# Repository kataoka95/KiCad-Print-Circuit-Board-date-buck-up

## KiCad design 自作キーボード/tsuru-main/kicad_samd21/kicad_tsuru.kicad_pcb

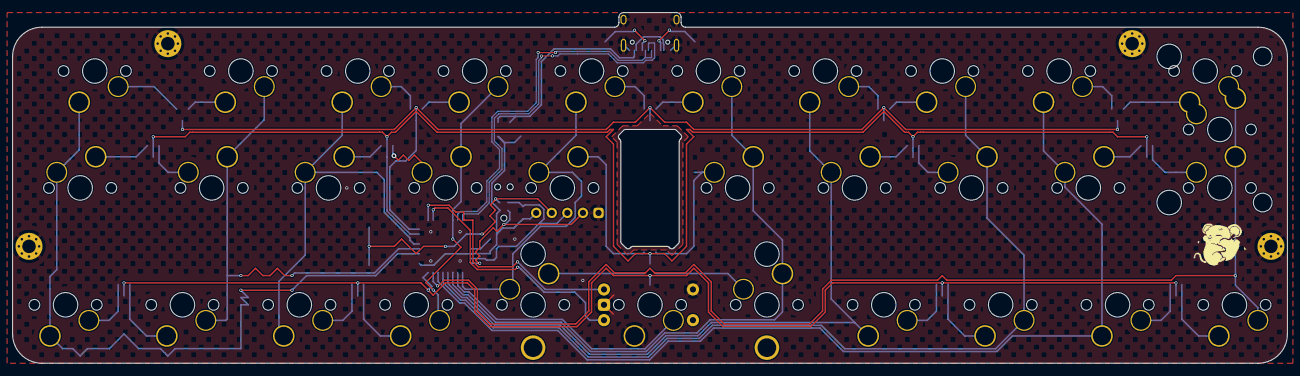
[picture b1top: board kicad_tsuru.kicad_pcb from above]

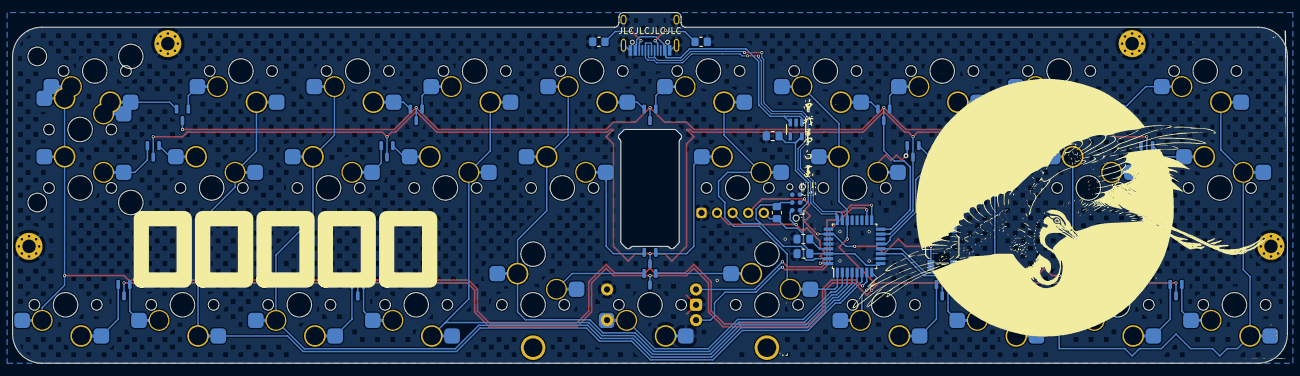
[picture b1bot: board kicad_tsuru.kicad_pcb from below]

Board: 2 copper layers, 207.8 x 57.2 mm, 67 parts (27 on the bottom side), 57 nets.

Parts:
C1, C3: 1nF; C_0805_2012Metric_Pad1.18x1.45mm_HandSolder
C2: 100nF; C_0805_2012Metric_Pad1.18x1.45mm_HandSolder
D1, D2, D3, D4, D5, D6, D7, D8, D9, D10, D11, D12, D13, D14, D15: BAV70_Small; apfel_SOT-23_silkless
H1, H2, H3, H4: MountingHole_Pad; MountingHole_2.2mm_M2_Pad_Via_nosilk
J1: USB_C_Receptacle_USB2.0; USB_C_Receptacle_GT-USB-7010
J2: Conn_ARM_SWD_TagConnect_TC2030-NL; Tag-Connect_TC2030-IDC-NL_2x03_P1.27mm_Vertical
J3: Conn_01x05_Pin; PinHeader_1x05_P2.54mm_Vertical
MX1, MX2, MX3, MX4, MX5, MX6, MX7, MX8, MX9, MX10, MX11, MX12, MX13, MX14, MX15, MX16, MX17, MX18, MX19, MX20, MX21, MX22, MX23, MX24, MX25, MX26, MX27, MX28, MX29, MX30, MX31, MX32: MX_SW_HS; MX-HotswapSAFE_no_silk
R1, R2: 5.1k; R_0805_2012Metric_Pad1.20x1.40mm_HandSolder
R3: 1k; R_0805_2012Metric_Pad1.20x1.40mm_HandSolder
S1: MX_stab; STAB_MX_P_3u
S2: MX_stab; STAB_MX_ISO-ROT
SW1: RotaryEncoder_Switch; ROT_Alps_EC11E-Switch_noMP_nosilk
SW2: SKQGAKE020; SW_SPST_SKQG_WithStem
U1: ATSAMD21E17D-A; TQFP-32_7x7mm_P0.8mm
U2: AP2112K-3.3; SOT-23-5
tsuru: LOGO

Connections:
+3.3V: C1.1, C2.1, J2.1 (VCC), J3.5, R3.1, U1.9 (VDDANA), U1.30 (VDDIN), U2.5 (VOUT)
+5V: J1.A4 (VBUS), J1.A9 (VBUS), J1.B4 (VBUS), J1.B9 (VBUS), U2.1 (VIN), U2.3 (EN)
D+: J1.A6 (D+), J1.B6 (D+), U1.24 (PA25)
D-: J1.A7 (D-), J1.B7 (D-), U1.23 (PA24)
ENC_LEFT: SW1.B, U1.18 (PA17)
ENC_RIGHT: SW1.A, U1.17 (PA16)
Enc_direct_pin: MX31.1, SW1.S1, U1.2 (PA01)
GND: C1.2, C2.2, C3.1, H1.1, H2.1, H3.1, H4.1, J1.A1 (GND), J1.A12 (GND), J1.B1 (GND), J1.B12 (GND), J1.S1 (SHIELD), J2.5 (GND), J3.1, MX31.2, R1.2, R2.2, SW1.C, SW1.S2, SW2.2, U1.10 (GND), U1.28 (GND), U2.2 (GND)
unnamed: D1.1 (A1), MX1.1
unnamed: D1.2 (A2), MX2.2
unnamed: D2.1 (A1), MX3.1
unnamed: D2.2 (A2), MX4.2
unnamed: D3.1 (A1), MX5.1
unnamed: D3.2 (A2), MX6.2
unnamed: D4.1 (A1), MX7.1
unnamed: D4.2 (A2), MX8.2
unnamed: D5.1 (A1), MX9.1
unnamed: D5.2 (A2), MX10.2, MX32.1
unnamed: D6.1 (A1), MX11.2
unnamed: D6.2 (A2), MX12.1
unnamed: D7.1 (A1), MX13.2
unnamed: D7.2 (A2), MX14.1
unnamed: D8.1 (A1), MX15.2
unnamed: D8.2 (A2), MX16.1
unnamed: D9.1 (A1), MX17.2
unnamed: D9.2 (A2), MX18.1
unnamed: D10.1 (A1), MX19.2
unnamed: D10.2 (A2), MX20.1
unnamed: D11.1 (A1), MX21.1
unnamed: D11.2 (A2), MX22.2
unnamed: D12.1 (A1), MX23.1
unnamed: D12.2 (A2), MX24.2
unnamed: D13.1 (A1), MX25.2
unnamed: D13.2 (A2), MX26.1
unnamed: D14.1 (A1), MX27.1
unnamed: D14.2 (A2), MX28.2
unnamed: D15.1 (A1), MX29.1
unnamed: D15.2 (A2), MX30.2
unnamed: J1.A5 (CC1), R1.1
unnamed: J1.B5 (CC2), R2.1
unnamed: C3.2, U1.29 (VDDCORE)
RESET: J2.3 (~RESET), J3.4, SW2.1, U1.26 (~RESET)
SWCLK: J2.4 (SWCLK), J3.3, R3.2, U1.31 (PA30)
SWDIO: J2.2 (SWDIO), J3.2, U1.32 (PA31)
c0: MX1.2, MX11.1, MX21.2, U1.11 (PA08)
c1: MX2.1, MX12.2, MX22.1, U1.12 (PA09)
c2: MX3.2, MX13.1, MX23.2, U1.13 (PA10)
c3: MX4.1, MX14.2, MX24.1, U1.22 (PA23)
c4: MX5.2, MX15.1, MX25.1, U1.1 (PA00)
c5: MX6.1, MX16.2, MX26.2, U1.3 (PA02)
c6: MX7.2, MX17.1, MX27.2, U1.4 (PA03)
c7: MX8.1, MX18.2, MX28.1, U1.5 (PA04)
c8: MX9.2, MX19.1, MX29.2, U1.6 (PA05)
c9: MX10.1, MX20.2, MX30.1, MX32.2, U1.7 (PA06)
r0: D1.3 (K), D2.3 (K), D3.3 (K), D4.3 (K), D5.3 (K), U1.16 (PA15)
r1: D6.3 (K), D7.3 (K), D8.3 (K), D9.3 (K), D10.3 (K), U1.15 (PA14)
r2: D11.3 (K), D12.3 (K), D13.3 (K), D14.3 (K), D15.3 (K), U1.8 (PA07)
